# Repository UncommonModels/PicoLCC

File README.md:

# Pico_LCC
Raspberry Pi Pico-based LCC Booster, with 2 i2c busses for add on cards using Qwiic connectors

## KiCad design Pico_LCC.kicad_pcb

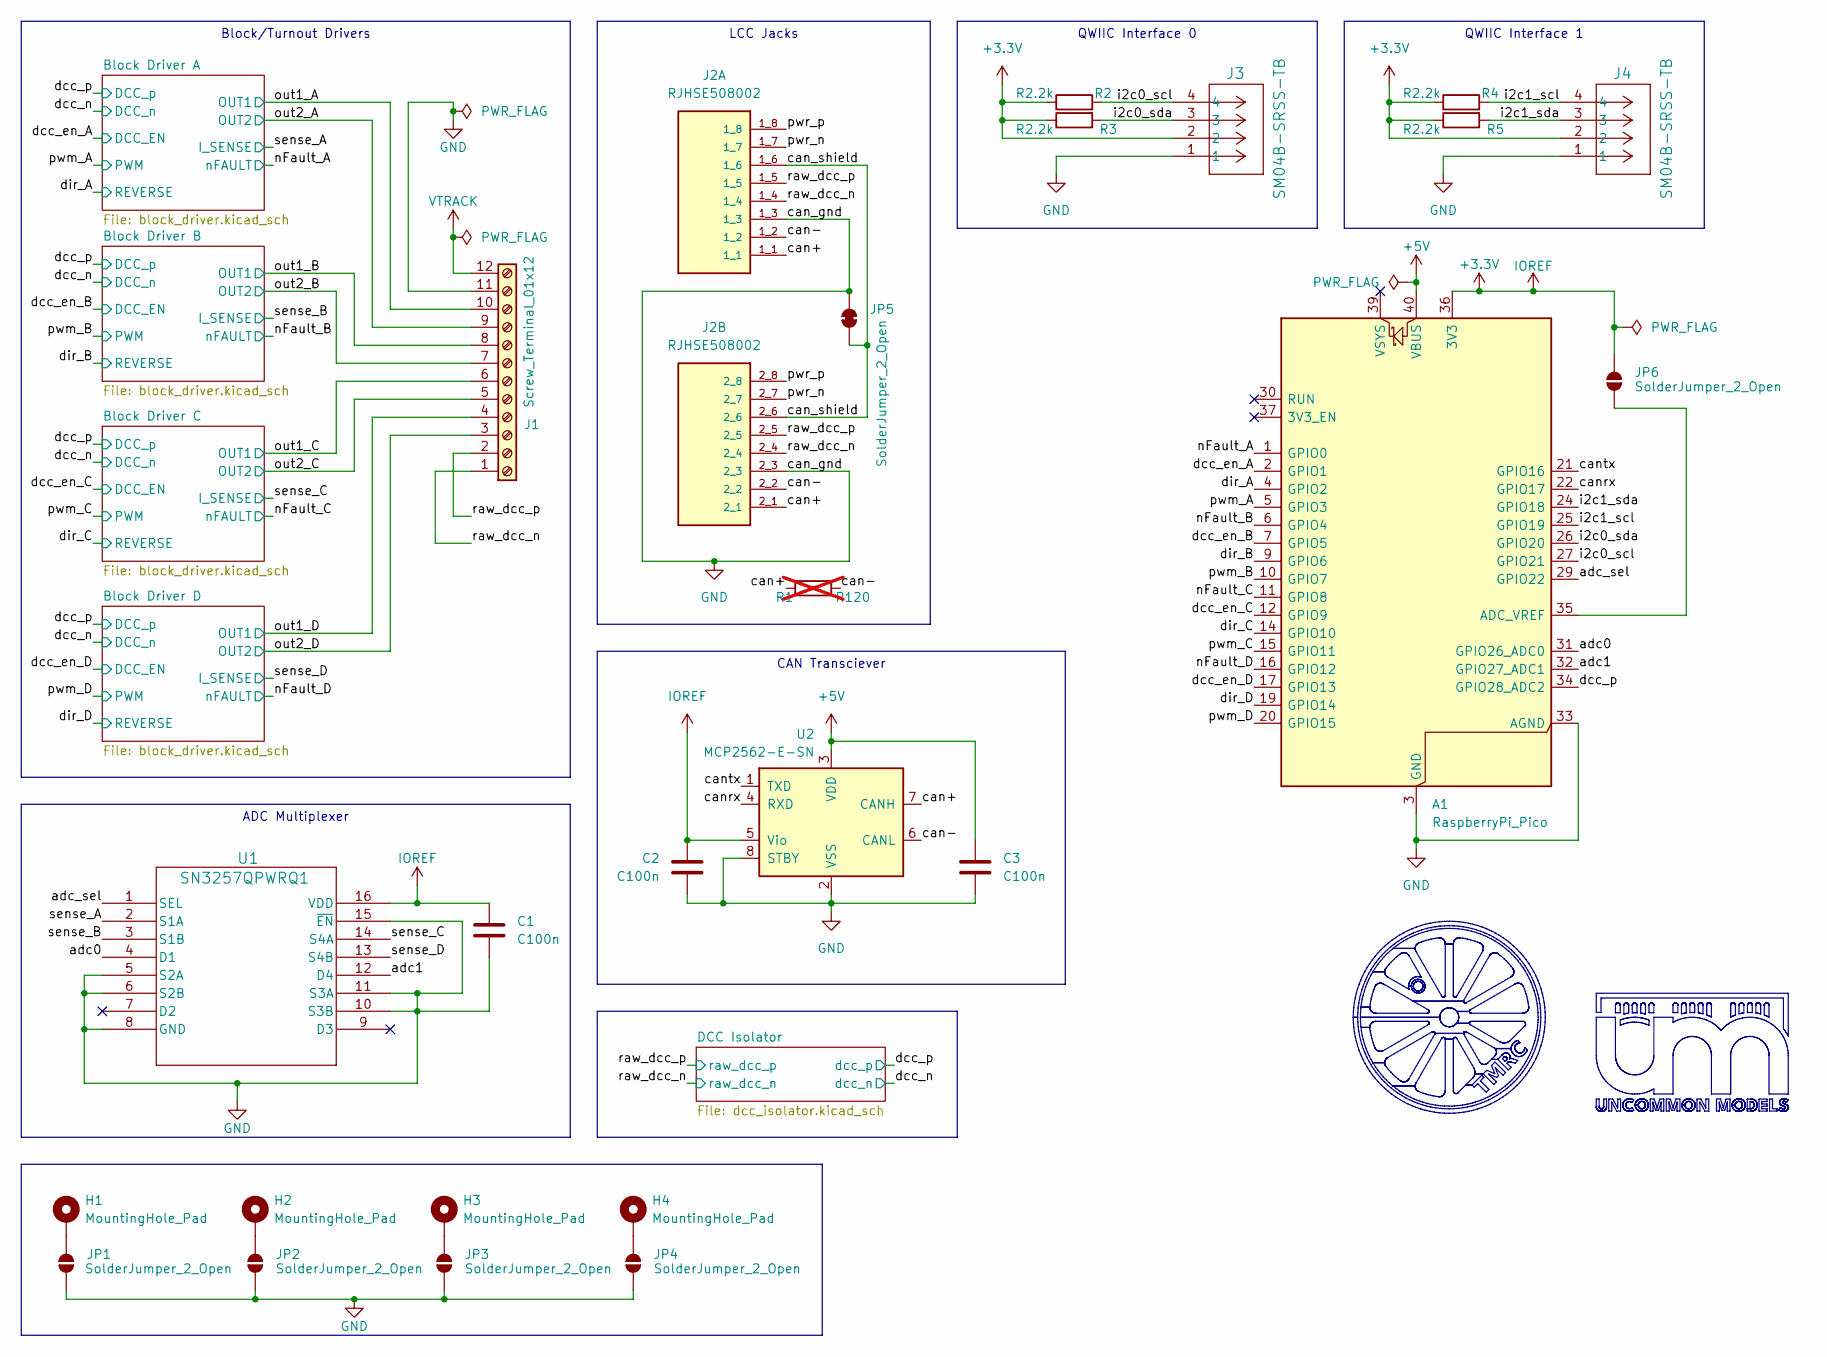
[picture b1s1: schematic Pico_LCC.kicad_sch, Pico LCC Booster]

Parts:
A1: RaspberryPi_Pico; RaspberryPi_Pico_Common_SMD
C1, C2, C3: C100n; C_0805_2012Metric_Pad1.18x1.45mm_HandSolder; Manufacturer Part Number CL21B104KACNFNC
H1, H2, H3, H4: MountingHole_Pad; MountingHole_4.3mm_M4_Pad_Via
J1: Screw_Terminal_01x12; TerminalBlock_Phoenix_MKDS-1,5-12_1x12_P5.00mm_Horizontal; Manufacturer Part Number 1753611
J2: RJHSE508002; AMPHENOL_RJHSE508002; PARTREV E
J3, J4: SM04B-SRSS-TB; CONN_SM04B-SRSS-TB_JST
JP1, JP2, JP3, JP4, JP6: SolderJumper_2_Open; SolderJumper-2_P1.3mm_Open_RoundedPad1.0x1.5mm
JP5: SolderJumper_2_Open; SolderJumper-2_P1.3mm_Bridged_RoundedPad1.0x1.5mm
R1: R120; R_0805_2012Metric_Pad1.20x1.40mm_HandSolder; Manufacturer Part Number ERJ6ENF4702V; not fitted
R2, R3, R4, R5: R2.2k; R_0805_2012Metric_Pad1.20x1.40mm_HandSolder; Manufacturer Part Number ERJ6ENF4702V
U1: SN3257QPWRQ1; SOIC_PRQ1_TEX
U2: MCP2562-E-SN; SOIC-8_3.9x4.9mm_P1.27mm; Manufacturer Part Number MCP2562-E-SN

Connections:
+3.3V: A1.36 (3V3), C1.1, C2.1, J3.2, J4.2, JP6.2 (B), R2.1, R3.1, R4.1, R5.1, U1.16 (VDD), U2.5 (Vio); also elsewhere on the board
+5V: A1.40 (VBUS), C3.1, U2.3 (VDD); also elsewhere on the board
/adc0: A1.31 (GPIO26_ADC0), U1.4 (D1)
/adc1: A1.32 (GPIO27_ADC1), U1.12 (D4)
/adc_sel: A1.29 (GPIO22), U1.1 (SEL)
/can+: J2.1_1, J2.2_1, R1.2, U2.7 (CANH)
/can-: J2.1_2, J2.2_2, R1.1, U2.6 (CANL)
/can_shield: J2.1_6, J2.2_6, JP5.1 (A)
/canrx: A1.22 (GPIO17), U2.4 (RXD)
/cantx: A1.21 (GPIO16), U2.1 (TXD)
/dcc_en_A: A1.2 (GPIO1); also elsewhere on the board
/dcc_en_B: A1.7 (GPIO5); also elsewhere on the board
/dcc_en_C: A1.12 (GPIO9); also elsewhere on the board
/dcc_en_D: A1.17 (GPIO13); also elsewhere on the board
/dcc_p: A1.34 (GPIO28_ADC2); also elsewhere on the board
/dir_A: A1.4 (GPIO2); also elsewhere on the board
/dir_B: A1.9 (GPIO6); also elsewhere on the board
/dir_C: A1.14 (GPIO10); also elsewhere on the board
/dir_D: A1.19 (GPIO14); also elsewhere on the board
/i2c0_scl: A1.27 (GPIO21), J3.4, R2.2
/i2c0_sda: A1.26 (GPIO20), J3.3, R3.2
/i2c1_scl: A1.25 (GPIO19), J4.4, R4.2
/i2c1_sda: A1.24 (GPIO18), J4.3, R5.2
/nFault_A: A1.1 (GPIO0); also elsewhere on the board
/nFault_B: A1.6 (GPIO4); also elsewhere on the board
/nFault_C: A1.11 (GPIO8); also elsewhere on the board
/nFault_D: A1.16 (GPIO12); also elsewhere on the board
/out1_A: J1.10; also elsewhere on the board
/out1_B: J1.8; also elsewhere on the board
/out1_C: J1.6; also elsewhere on the board
/out1_D: J1.4; also elsewhere on the board
/out2_A: J1.9; also elsewhere on the board
/out2_B: J1.7; also elsewhere on the board
/out2_C: J1.5; also elsewhere on the board
/out2_D: J1.3; also elsewhere on the board
/pwm_A: A1.5 (GPIO3); also elsewhere on the board
/pwm_B: A1.10 (GPIO7); also elsewhere on the board
/pwm_C: A1.15 (GPIO11); also elsewhere on the board
/pwm_D: A1.20 (GPIO15); also elsewhere on the board
/pwr_n: J2.1_7, J2.2_7
/pwr_p: J2.1_8, J2.2_8
/raw_dcc_n: J1.1, J2.1_4, J2.2_4; also elsewhere on the board
/raw_dcc_p: J1.2, J2.1_5, J2.2_5; also elsewhere on the board
/sense_A: U1.2 (S1A); also elsewhere on the board
/sense_B: U1.3 (S1B); also elsewhere on the board
/sense_C: U1.14 (S4A); also elsewhere on the board
/sense_D: U1.13 (S4B); also elsewhere on the board
GND: A1.3 (GND), A1.8 (GND), A1.13 (GND), A1.18 (GND), A1.23 (GND), A1.28 (GND), A1.33 (AGND), A1.38 (GND), C1.2, C2.2, C3.2, J1.11, J2.1_3, J2.2_3, J3.1, J4.1, JP1.1 (A), JP2.1 (A), JP3.1 (A), JP4.1 (A), JP5.2 (B), U1.5 (S2A), U1.6 (S2B), U1.8 (GND), U1.10 (S3B), U1.11 (S3A), U1.15 (~EN), U2.2 (VSS), U2.8 (STBY); also elsewhere on the board
unnamed: A1.35 (ADC_VREF), JP6.1 (A)
unnamed: H1.1, JP1.2 (B)
unnamed: H2.1, JP2.2 (B)
unnamed: H3.1, JP3.2 (B)
unnamed: H4.1, JP4.2 (B)
VTRACK: J1.12; also elsewhere on the board

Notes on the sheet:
CAN Transciever
Block/Turnout Drivers
QWIIC Interface 0
LCC Jacks
ADC Multiplexer
QWIIC Interface 1

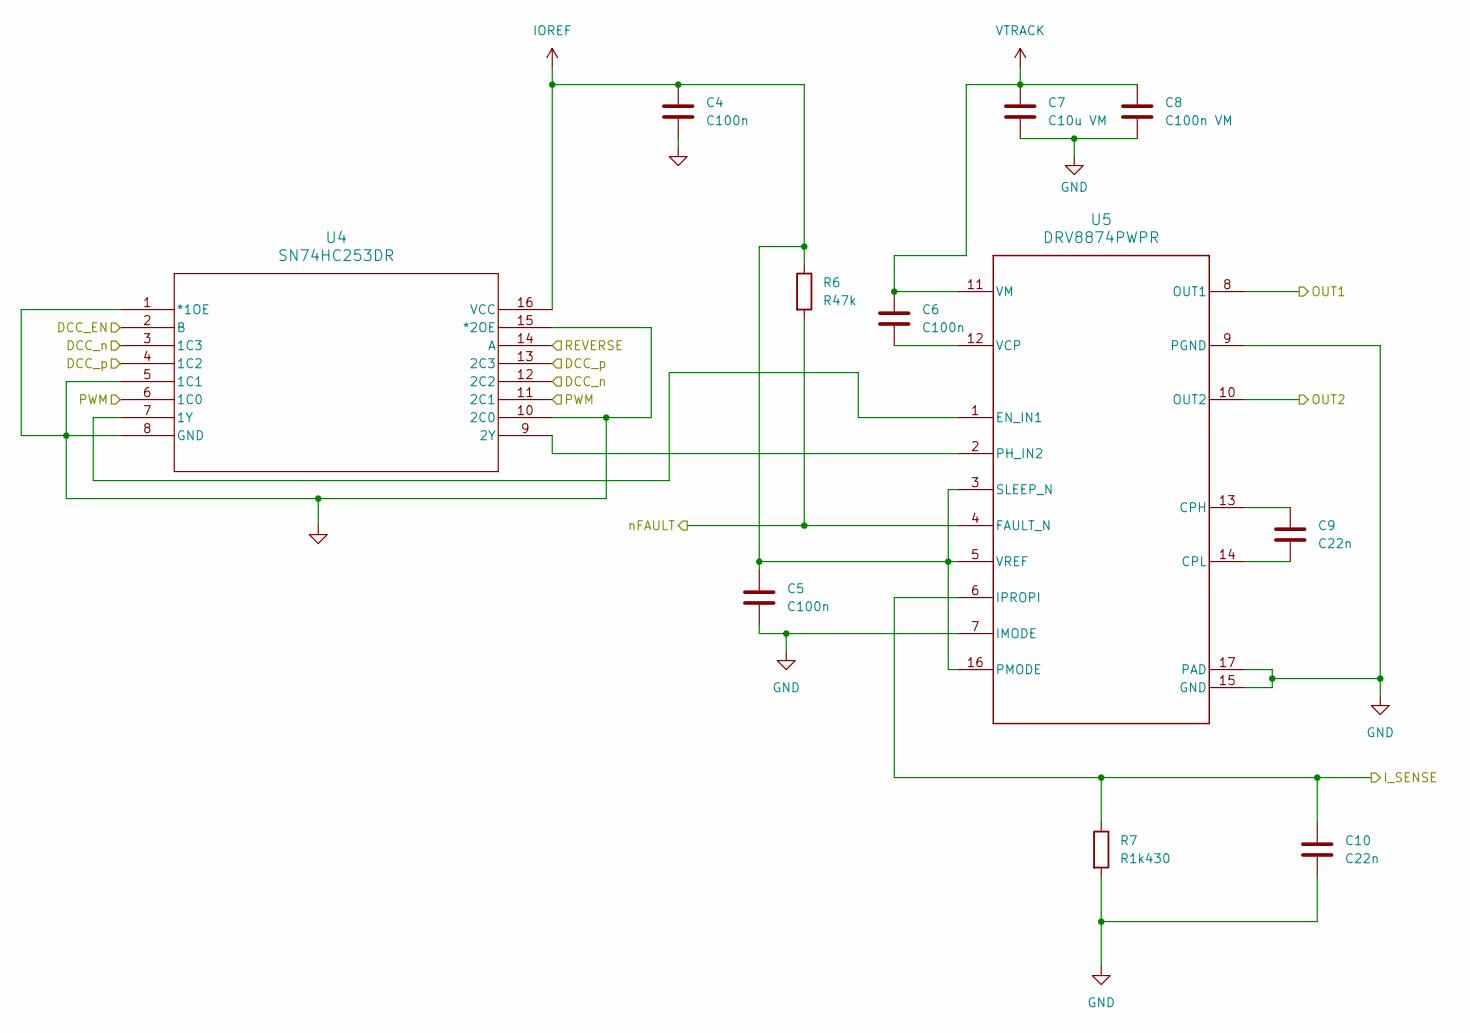
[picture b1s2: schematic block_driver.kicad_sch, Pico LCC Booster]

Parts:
C4, C5, C6: C100n; C_0805_2012Metric_Pad1.18x1.45mm_HandSolder; Manufacturer Part Number CL21B104KACNFNC
C7: C10u VM; C_1206_3216Metric_Pad1.33x1.80mm_HandSolder; Manufacturer Part Number CL31A106KBHNNNE
C8: C100n VM; C_0805_2012Metric_Pad1.18x1.45mm_HandSolder; Manufacturer Part Number CL21B104KBFXPJE
C9, C10: C22n; C_0805_2012Metric_Pad1.18x1.45mm_HandSolder; Manufacturer Part Number CL21B223JBANNNC
R6: R47k; R_0805_2012Metric_Pad1.20x1.40mm_HandSolder; Manufacturer Part Number ERJ6ENF4702V
R7: R1k430; R_0805_2012Metric_Pad1.20x1.40mm_HandSolder; Manufacturer Part Number RC0805FR-071K43L
U4: SN74HC253DR; SO-16_3.9x9.9mm_P1.27mm; Manufacturer Part Number SN74HC253DR
U5: DRV8874PWPR; PWP0016J_NV; Manufacturer Part Number DRV8874PWPR

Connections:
+3.3V: C4.1, C5.1, R6.1, U4.16 (VCC), U5.3 (SLEEP_N), U5.5 (VREF), U5.16 (PMODE); also elsewhere on the board
/dcc_en_A: U4.2 (B); also elsewhere on the board
/dcc_n: U4.3 (1C3), U4.12 (2C2); also elsewhere on the board
/dcc_p: U4.4 (1C2), U4.13 (2C3); also elsewhere on the board
/dir_A: U4.14 (A); also elsewhere on the board
/nFault_A: R6.2, U5.4 (FAULT_N); also elsewhere on the board
/out1_A: U5.8 (OUT1); also elsewhere on the board
/out2_A: U5.10 (OUT2); also elsewhere on the board
/pwm_A: U4.6 (1C0), U4.11 (2C1); also elsewhere on the board
/sense_A: C10.1, R7.1, U5.6 (IPROPI); also elsewhere on the board
GND: C4.2, C5.2, C7.2, C8.2, C10.2, R7.2, U4.1 (*1OE), U4.5 (1C1), U4.8 (GND), U4.10 (2C0), U4.15 (*2OE), U5.7 (IMODE), U5.9 (PGND), U5.15 (GND), U5.17 (PAD); also elsewhere on the board
unnamed: U4.7 (1Y), U5.1 (EN_IN1)
unnamed: U4.9 (2Y), U5.2 (PH_IN2)
unnamed: C9.1, U5.13 (CPH)
unnamed: C9.2, U5.14 (CPL)
unnamed: C6.2, U5.12 (VCP)
VTRACK: C6.1, C7.1, C8.1, U5.11 (VM); also elsewhere on the board

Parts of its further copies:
C11, C12, C13, C18, C19, C20, C25, C26, C27: C100n; C_0805_2012Metric_Pad1.18x1.45mm_HandSolder; Manufacturer Part Number CL21B104KACNFNC
C14, C21, C28: C10u VM; C_1206_3216Metric_Pad1.33x1.80mm_HandSolder; Manufacturer Part Number CL31A106KBHNNNE
C15, C22, C29: C100n VM; C_0805_2012Metric_Pad1.18x1.45mm_HandSolder; Manufacturer Part Number CL21B104KBFXPJE
C16, C17, C23, C24, C30, C31: C22n; C_0805_2012Metric_Pad1.18x1.45mm_HandSolder; Manufacturer Part Number CL21B223JBANNNC
R8, R10, R12: R47k; R_0805_2012Metric_Pad1.20x1.40mm_HandSolder; Manufacturer Part Number ERJ6ENF4702V
R9, R11, R13: R1k430; R_0805_2012Metric_Pad1.20x1.40mm_HandSolder; Manufacturer Part Number RC0805FR-071K43L
U6, U8, U10: SN74HC253DR; SO-16_3.9x9.9mm_P1.27mm; Manufacturer Part Number SN74HC253DR
U7, U9, U11: DRV8874PWPR; PWP0016J_NV; Manufacturer Part Number DRV8874PWPR

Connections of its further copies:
+3.3V: C11.1, C12.1, C18.1, C19.1, C25.1, C26.1, R8.1, R10.1, R12.1, U6.16 (VCC), U7.3 (SLEEP_N), U7.5 (VREF), U7.16 (PMODE), U8.16 (VCC), U9.3 (SLEEP_N), U9.5 (VREF), U9.16 (PMODE), U10.16 (VCC), U11.3 (SLEEP_N), U11.5 (VREF), U11.16 (PMODE); also elsewhere on the board
/dcc_en_B: U6.2 (B); also elsewhere on the board
/dcc_en_C: U8.2 (B); also elsewhere on the board
/dcc_en_D: U10.2 (B); also elsewhere on the board
/dcc_n: U6.3 (1C3), U6.12 (2C2), U8.3 (1C3), U8.12 (2C2), U10.3 (1C3), U10.12 (2C2); also elsewhere on the board
/dcc_p: U6.4 (1C2), U6.13 (2C3), U8.4 (1C2), U8.13 (2C3), U10.4 (1C2), U10.13 (2C3); also elsewhere on the board
/dir_B: U6.14 (A); also elsewhere on the board
/dir_C: U8.14 (A); also elsewhere on the board
/dir_D: U10.14 (A); also elsewhere on the board
/nFault_B: R8.2, U7.4 (FAULT_N); also elsewhere on the board
/nFault_C: R10.2, U9.4 (FAULT_N); also elsewhere on the board
/nFault_D: R12.2, U11.4 (FAULT_N); also elsewhere on the board
/out1_B: U7.8 (OUT1); also elsewhere on the board
/out1_C: U9.8 (OUT1); also elsewhere on the board
/out1_D: U11.8 (OUT1); also elsewhere on the board
/out2_B: U7.10 (OUT2); also elsewhere on the board
/out2_C: U9.10 (OUT2); also elsewhere on the board
/out2_D: U11.10 (OUT2); also elsewhere on the board
/pwm_B: U6.6 (1C0), U6.11 (2C1); also elsewhere on the board
/pwm_C: U8.6 (1C0), U8.11 (2C1); also elsewhere on the board
/pwm_D: U10.6 (1C0), U10.11 (2C1); also elsewhere on the board
/sense_B: C17.1, R9.1, U7.6 (IPROPI); also elsewhere on the board
/sense_C: C24.1, R11.1, U9.6 (IPROPI); also elsewhere on the board
/sense_D: C31.1, R13.1, U11.6 (IPROPI); also elsewhere on the board
GND: C11.2, C12.2, C14.2, C15.2, C17.2, C18.2, C19.2, C21.2, C22.2, C24.2, C25.2, C26.2, C28.2, C29.2, C31.2, R9.2, R11.2, R13.2, U6.1 (*1OE), U6.5 (1C1), U6.8 (GND), U6.10 (2C0), U6.15 (*2OE), U7.7 (IMODE), U7.9 (PGND), U7.15 (GND), U7.17 (PAD), U8.1 (*1OE), U8.5 (1C1), U8.8 (GND), U8.10 (2C0), U8.15 (*2OE), U9.7 (IMODE), U9.9 (PGND), U9.15 (GND), U9.17 (PAD), U10.1 (*1OE), U10.5 (1C1), U10.8 (GND), U10.10 (2C0), U10.15 (*2OE), U11.7 (IMODE), U11.9 (PGND), U11.15 (GND), U11.17 (PAD); also elsewhere on the board
unnamed: U6.7 (1Y), U7.1 (EN_IN1)
unnamed: U6.9 (2Y), U7.2 (PH_IN2)
unnamed: C16.1, U7.13 (CPH)
unnamed: C16.2, U7.14 (CPL)
unnamed: C13.2, U7.12 (VCP)
unnamed: U8.7 (1Y), U9.1 (EN_IN1)
unnamed: U8.9 (2Y), U9.2 (PH_IN2)
unnamed: C23.1, U9.13 (CPH)
unnamed: C23.2, U9.14 (CPL)
unnamed: C20.2, U9.12 (VCP)
unnamed: U10.7 (1Y), U11.1 (EN_IN1)
unnamed: U10.9 (2Y), U11.2 (PH_IN2)
unnamed: C30.1, U11.13 (CPH)
unnamed: C30.2, U11.14 (CPL)
unnamed: C27.2, U11.12 (VCP)
VTRACK: C13.1, C14.1, C15.1, C20.1, C21.1, C22.1, C27.1, C28.1, C29.1, U7.11 (VM), U9.11 (VM), U11.11 (VM); also elsewhere on the board

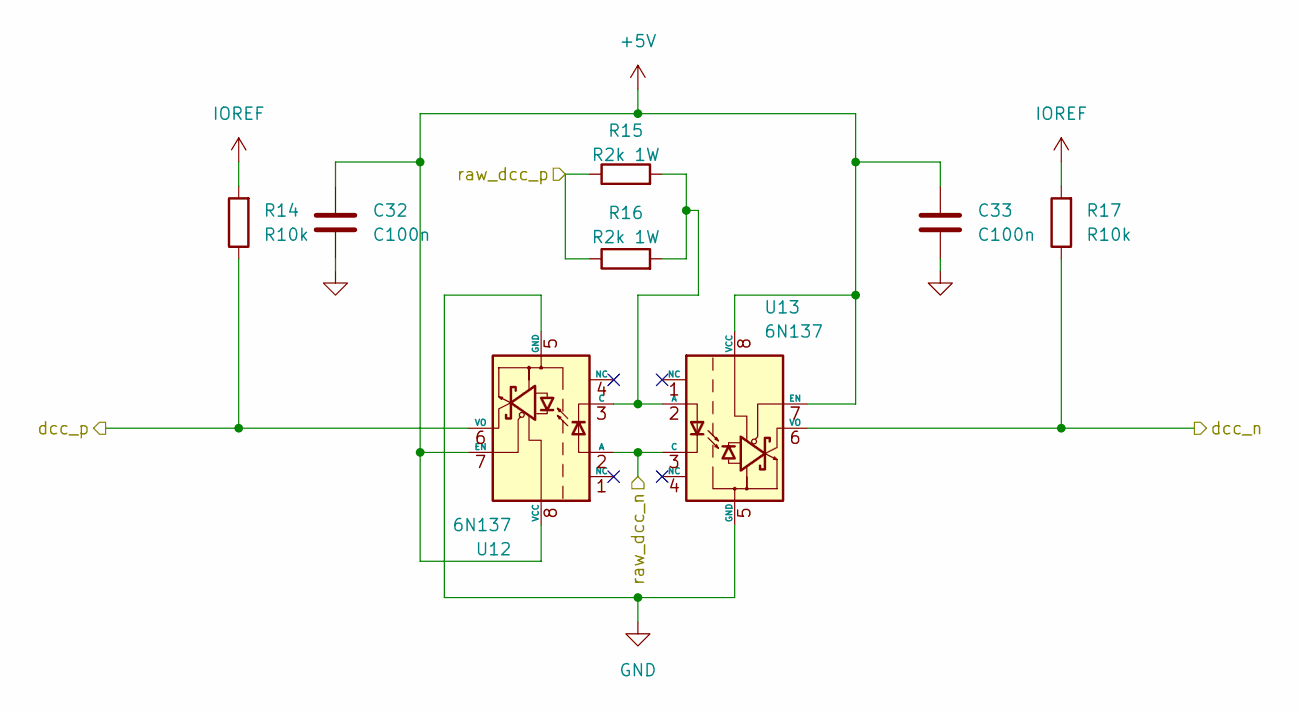
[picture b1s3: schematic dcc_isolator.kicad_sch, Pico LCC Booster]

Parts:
C32, C33: C100n; C_0805_2012Metric_Pad1.18x1.45mm_HandSolder; Manufacturer Part Number CL21B104KACNFNC
R14, R17: R10k; R_0805_2012Metric_Pad1.20x1.40mm_HandSolder; Manufacturer Part Number RC0805JR-0710KL
R15, R16: R2k 1W; R_2512_6332Metric_Pad1.40x3.35mm_HandSolder; Manufacturer Part Number AC2512JK-072KL
U12, U13: 6N137; DIP-8_W7.62mm_SMDSocket_SmallPads; Manufacturer Part Number 6N137S-TA1-L

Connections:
+3.3V: R14.2, R17.2; also elsewhere on the board
+5V: C32.1, C33.1, U12.7 (EN), U12.8 (VCC), U13.7 (EN), U13.8 (VCC); also elsewhere on the board
/dcc_n: R17.1, U13.6 (VO); also elsewhere on the board
/dcc_p: R14.1, U12.6 (VO); also elsewhere on the board
/raw_dcc_n: U12.2 (A), U13.3 (C); also elsewhere on the board
/raw_dcc_p: R15.1, R16.1; also elsewhere on the board
GND: C32.2, C33.2, U12.5 (GND), U13.5 (GND); also elsewhere on the board
unnamed: R15.2, R16.2, U12.3 (C), U13.2 (A)

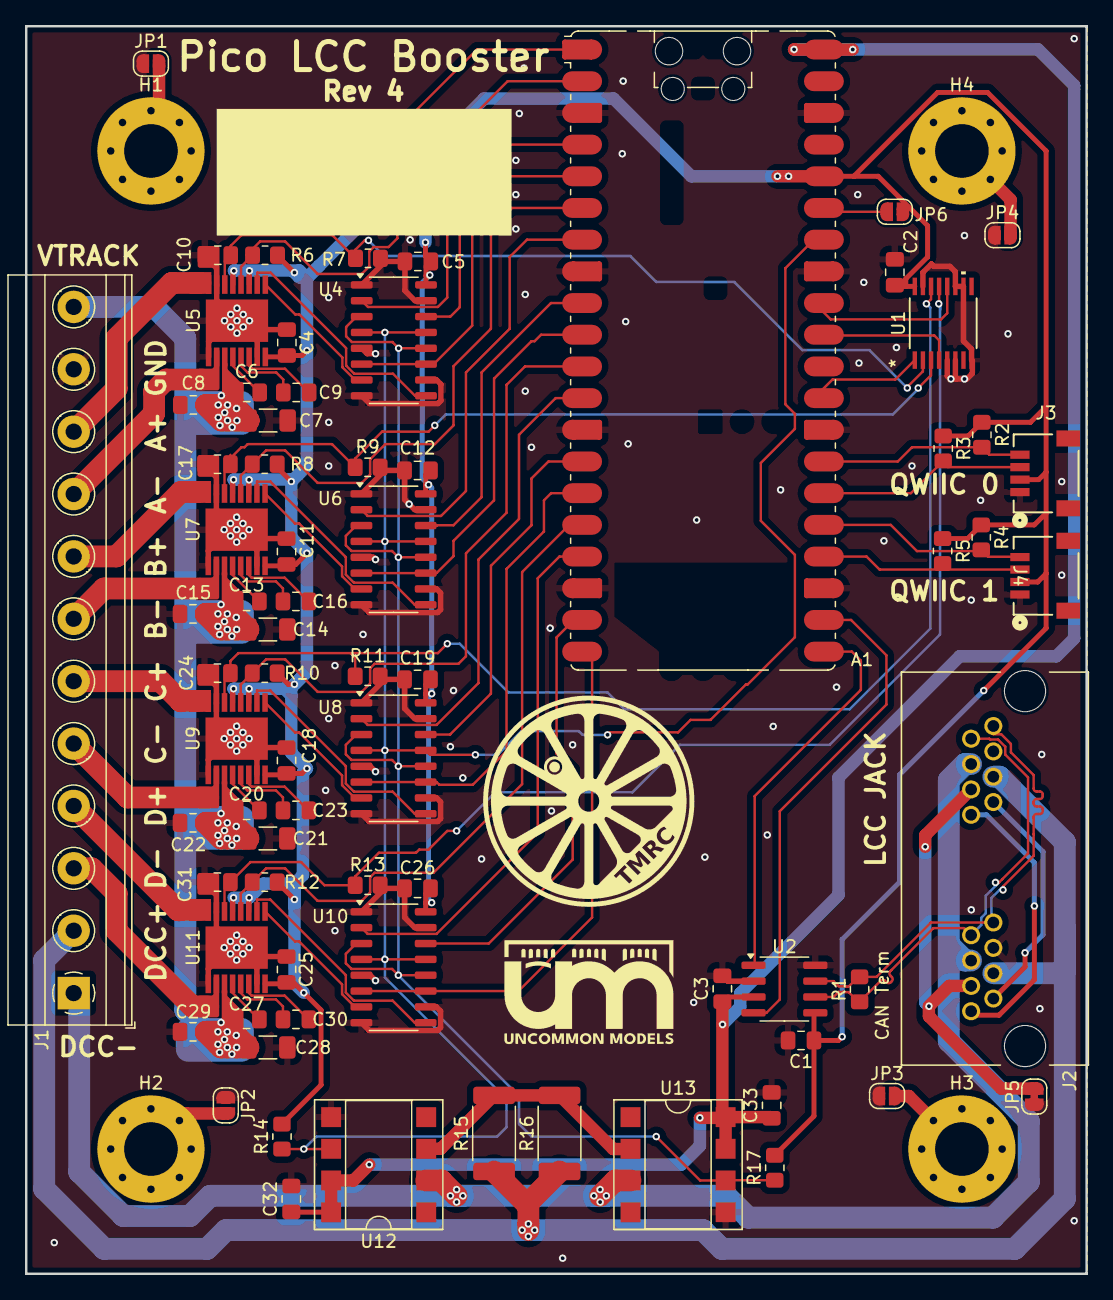
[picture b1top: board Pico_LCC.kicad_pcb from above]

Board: 2 copper layers, 85.0 x 100.0 mm, 77 parts (0 on the bottom side), 76 nets.

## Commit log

2025-01-28 Add Render
2025-02-03 Update Including Revisions 1.1 and 2
2025-04-07 v4 with Stencil and Frame
